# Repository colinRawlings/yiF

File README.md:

# The yiF
*a foolish combination of action cameras and SLR lenses*

## introduction 

This is a project seeking to replace an action cameras fisheye lens with one of the low cost plastic bodied EFs STM zoom lenses from Canon.  Ideally this combines the action camera's high frame rates (HD at 240 frames/second) with the lens' zoom, depth of field control and active image stabilisation.  Some example footage is here:

The lens is controlled via an Arduino micro and a Yi 4k+ was used for the action camera.  Via the arduino the lens' focus, aperture and image stabilisation motors can be controlled.  The housing is 3D printed and a commlite EF-EOSM adaptor is used for mounting the lens.

For video monitoring the Yi's in-built display combined with an optical viewfinder (the kinotehnik LCDVF 3/2) or an external monitor (smartphone or the ikan VL35) was used.  

The system was tested with several of the EFs STM lenses (10-18 mm, 18-135 mm f3.5 and 55-250 mm f4) and a sigma 35 mm f1.4. The system exhibits a roughly 3x crop sensor, this amplifies the available travel of the image stabiliser, increases the reach of the lens and improves the depth of field control.  

So far nothing bad has happened to the lenses however: 

**You can apparently burn the aperture motor in Canon lenses quite easily.**

*I take no responsibility for any damage caused by the things in this repo.*

The starting point for this work was this article:

https://pickandplace.wordpress.com/2011/10/05/canon-ef-s-protocol-and-electronic-follow-focus/

from here I used a Saleae logic analyser to record the conversations between the lenses and a 650D.  These were then analysed in Matlab since in particular I needed the command to start the image stabilisation motor and activate the manual focus ring (the STM lenses are “focus by wire”).

## code

This comes in several parts

* A python class for communicating over usb (/serial port) with the arduino.
* [The arduino code](https://github.com/colinRawlings/yiFu)
* The matlab (/octave?) code for parsing the csv files generated by the logic analyser

## cad

The cad was done in Fusion (free for the first year).  The assembly is here: http://a360.co/2sxdWEE

the stl files for printing are in cad/fab.  They are only suitable for selective laser sintering or HP jet fusion of nylon.  I used [3Dhubs.com](https://www.3dhubs.com) to find a nearby printer.

## electronics

The electronics design was done in kicad.  Note the arduino can control the power to the lens.  The entire lens is switch off after each movement of the aperture motor rather than relying on the motor off command being successfully received.  The gerber files are in elec/fab.  I eventually settled on powering the system with an LP-E6 camera battery.

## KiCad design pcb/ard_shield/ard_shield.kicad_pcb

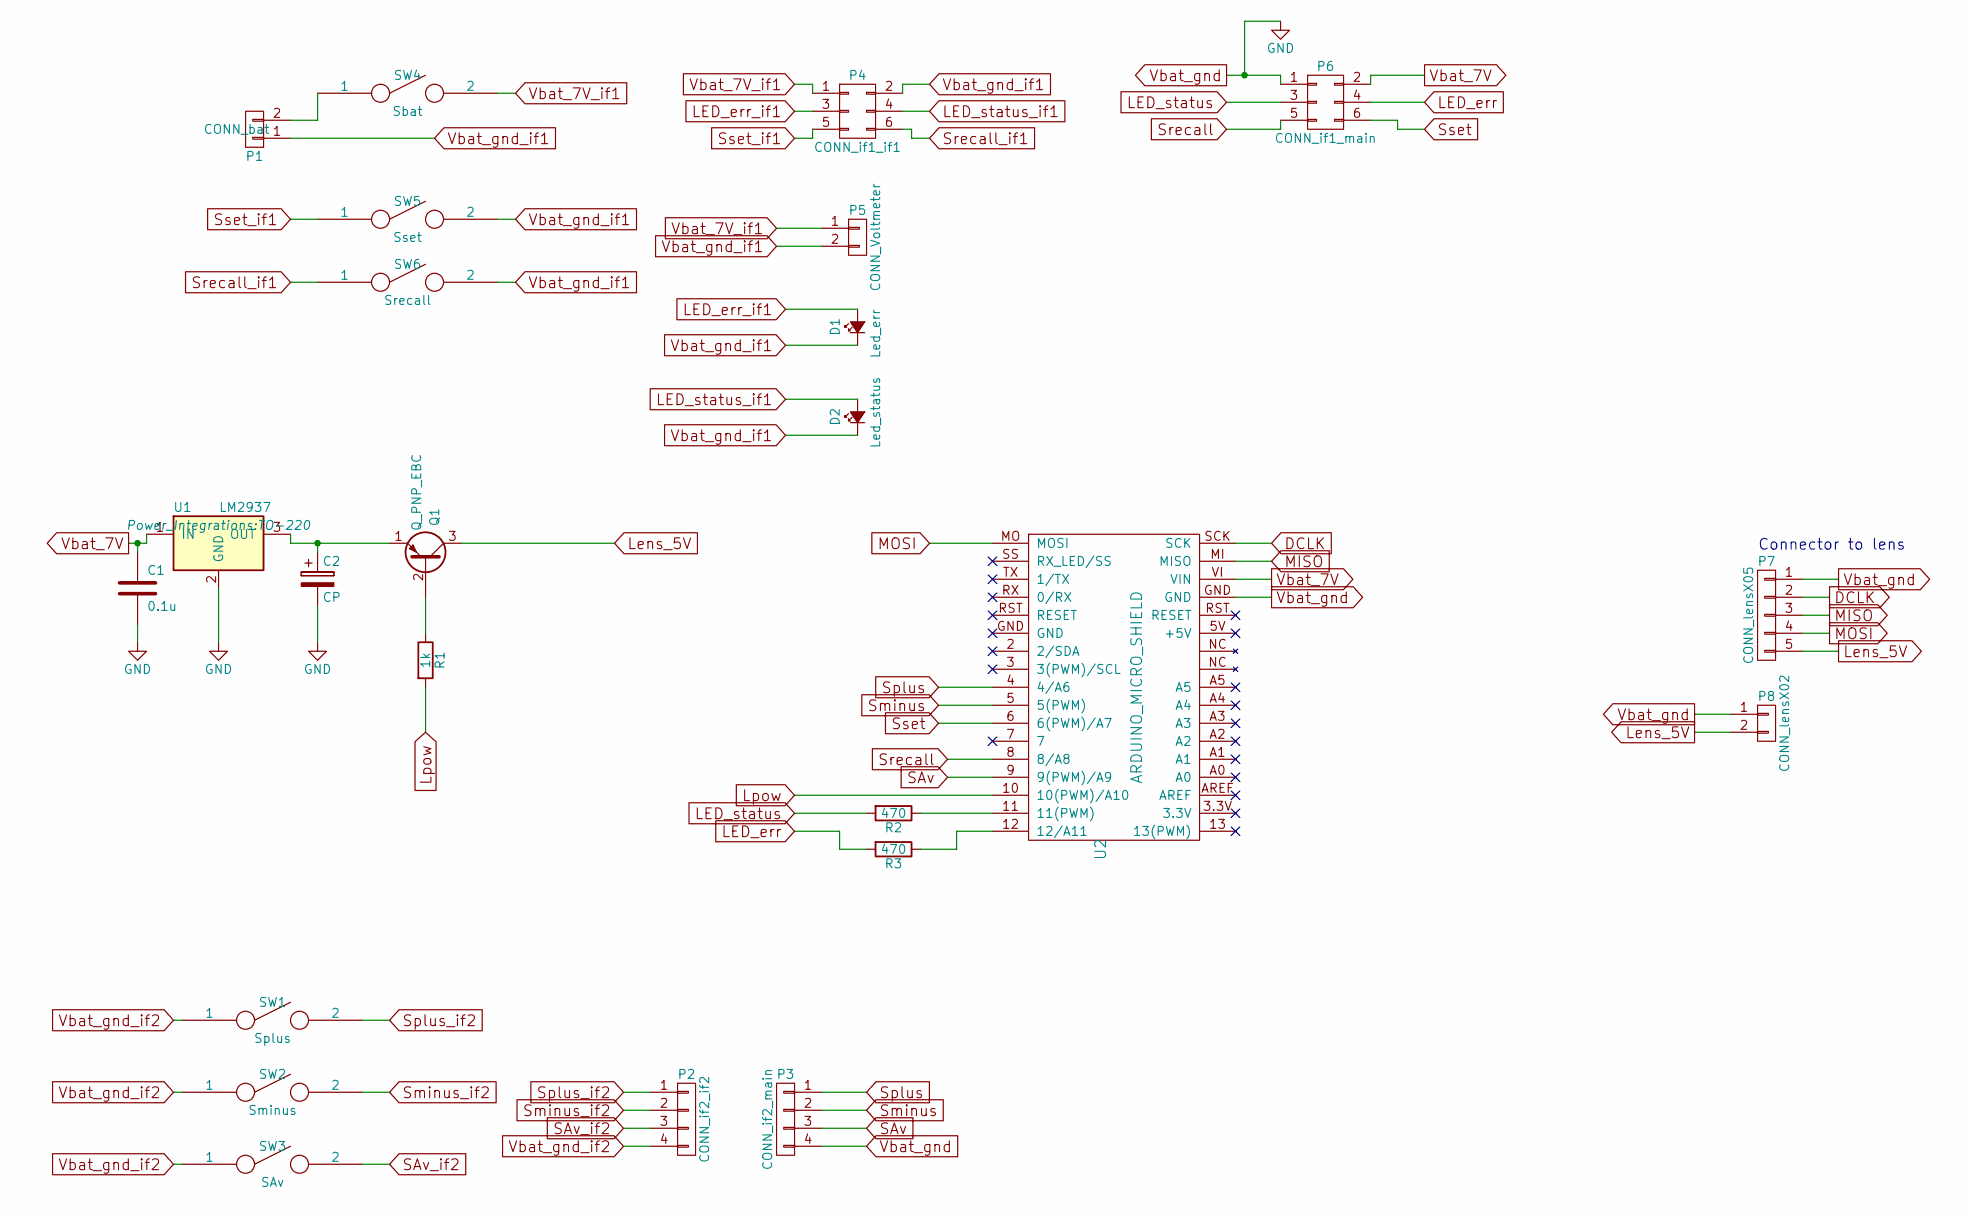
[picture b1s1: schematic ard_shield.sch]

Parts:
C1: 0.1u; C_Disc_D3_P2.5
C2: CP; C_Rect_L7_W2_P5
D1: Led_err; LED-3MM
D2: Led_status; LED-3MM
P1: CONN_bat; Pin_Header_Angled_1x02
P2: CONN_if2_if2; Pin_Header_Angled_1x04
P3: CONN_if2_main; Socket_Strip_Angled_1x04
P4: CONN_if1_if1; Socket_Strip_Straight_2x03
P5: CONN_Voltmeter; Pin_Header_Straight_1x02
P6: CONN_if1_main; Pin_Header_Straight_2x03
P7: CONN_lensX05; Socket_Strip_Angled_1x05
P8: CONN_lensX02; Socket_Strip_Angled_1x02
Q1: Q_PNP_EBC
R1: 1k; Resistor_Horizontal_RM7mm
R2, R3: 470; Resistor_Horizontal_RM7mm
SW1: Splus; SW_PUSH-12mm
SW2: Sminus; SW_PUSH-12mm
SW3: SAv; SW_PUSH-12mm
SW4: Sbat; SW_Matias_Quiet
SW5: Sset; SW_PUSH-12mm
SW6: Srecall; SW_PUSH-12mm
U1: LM2937; TO-220
U2: ARDUINO_MICRO_SHIELD

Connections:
DCLK: P7.2, U2.SCK
LED_err: P6.4, R3.2
LED_err_if1: D1.2 (A), P4.3
LED_status: P6.3, R2.2
LED_status_if1: D2.2 (A), P4.4
Lens_5V: P7.5, P8.2, Q1.3 (C)
Lpow: R1.2, U2.10 (10(PWM)/A10)
MISO: P7.3, U2.MI (MISO)
MOSI: P7.4, U2.MO (MOSI)
unnamed: C2.1, Q1.1 (E), U1.3 (OUT)
unnamed: P1.2, SW4.1
unnamed: Q1.2 (B), R1.1
unnamed: R2.1, U2.11 (11(PWM))
unnamed: R3.1, U2.12 (12/A11)
SAv: P3.3, U2.9 (9(PWM)/A9)
SAv_if2: P2.3, SW3.2
Sminus: P3.2, U2.5 (5(PWM))
Sminus_if2: P2.2, SW2.2
Splus: P3.1, U2.4 (4/A6)
Splus_if2: P2.1, SW1.2
Srecall: P6.5, U2.8 (8/A8)
Srecall_if1: P4.6, SW6.1
Sset: P6.6, U2.6 (6(PWM)/A7)
Sset_if1: P4.5, SW5.1
Vbat_7V: C1.1, P6.2, U1.1 (IN), U2.VI (VIN)
Vbat_7V_if1: P4.1, P5.1, SW4.2
Vbat_gnd: C1.2, C2.2, P3.4, P6.1, P7.1, P8.1, U1.2 (GND), U2.GND
Vbat_gnd_if1: D1.1 (K), D2.1 (K), P1.1, P4.2, P5.2, SW5.2, SW6.2
Vbat_gnd_if2: P2.4, SW1.1, SW2.1, SW3.1

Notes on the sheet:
Connector to lens

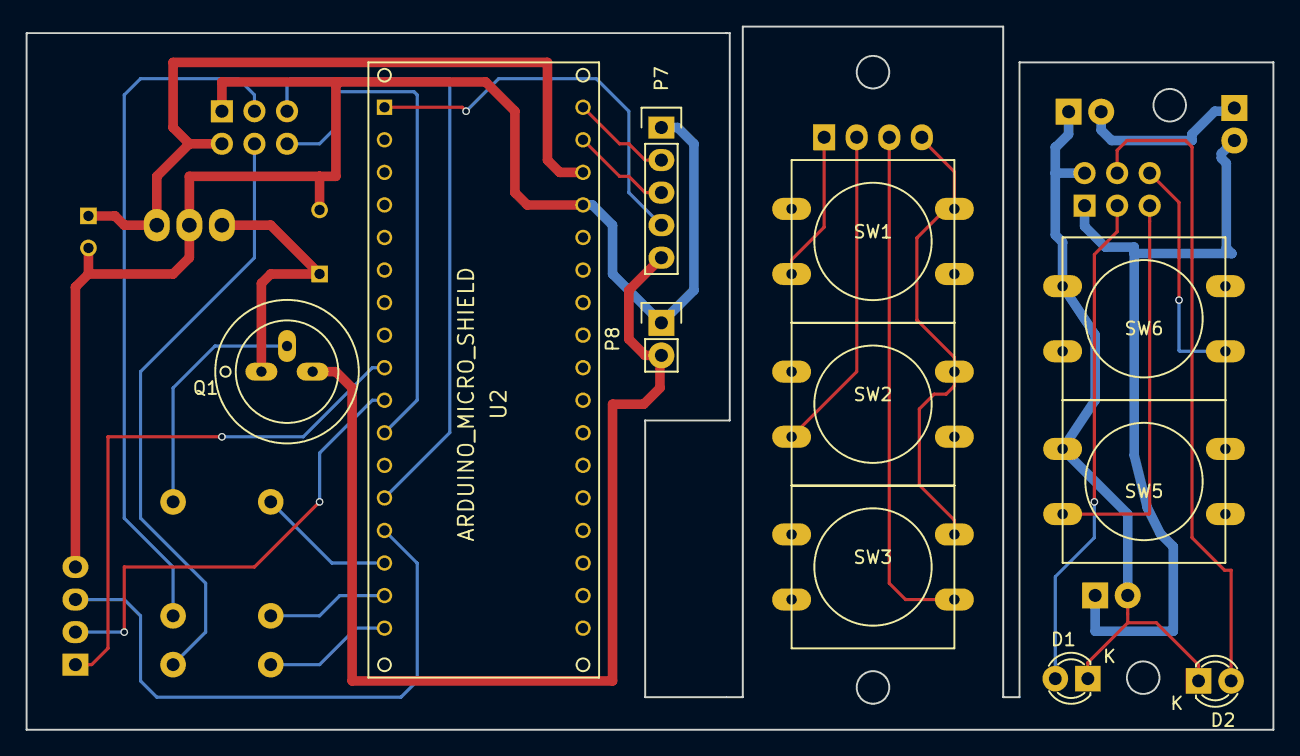
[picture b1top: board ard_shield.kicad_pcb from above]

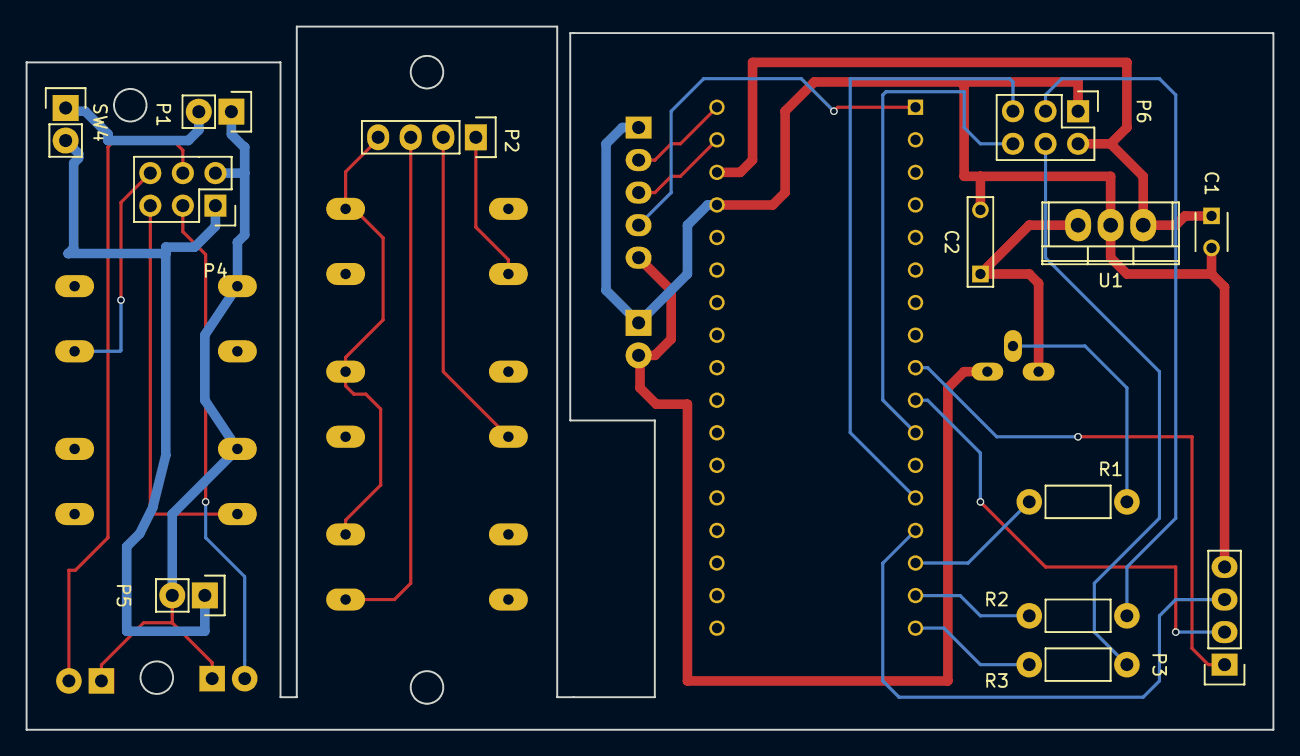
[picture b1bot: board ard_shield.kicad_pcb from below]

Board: 2 copper layers, 97.3 x 54.9 mm, 24 parts (13 on the bottom side), 29 nets.

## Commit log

2017-07-07 Initial commit: cad and elec files
    also python files
2017-07-12 Test gif in README
2017-08-02 add submodule for arduino oop code
2017-09-10 - improved error checking in py code - add current state of arduino code
2017-09-11 Minor change to README.md
2017-09-21 small update to README
2018-01-14 changes for new casing
